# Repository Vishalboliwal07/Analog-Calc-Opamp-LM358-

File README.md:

# Analog Calculator

## Summary
In a world dominated by digital microprocessors, this project explores the principles of analog computing by designing and constructing a functional, purely analog calculator. The core of the system is built around LM358 operational amplifiers configured with specific feedback networks of resistors, capacitors, and diodes. The calculator operates as a parallel processing system where all calculations happen simultaneously based on variable DC voltage or AC signal inputs. The system operates on a dual-rail +/-15V or 30V power supply, establishing a true 0V ground reference to simplify the circuit designs and eliminate the need for a virtual ground.

*Note regarding the power supply: While some project documentation may refer to a +/-30V power rail, the system actually operates on a +/-15V dual-rail supply (which provides a total 30V potential difference). This establishes a true 0V ground reference to simplify the circuit designs and eliminate the need for a virtual ground.*

## Mathematical Functions Supported
The calculator accepts numerical inputs (from 0.01V to 14V) and implements dedicated modular circuits to perform the following operations:
* **Addition:** Utilizes an inverting summing amplifier.
* **Subtraction:** Utilizes a difference amplifier to find the difference between two signals.
* **Multiplication:** Achieved using logarithmic principles (In(A * B) = In(A) + In(B)) via log, summing, and anti-log stages.
* **Division:** Similar to multiplication, but uses a subtraction (difference) stage for the log values.
* **Logarithm:** Uses the exponential current-voltage relationship of a semiconductor diode in the op-amp's feedback path.
* **Anti-Logarithm (Exponential):** Performs the inverse operation of the log amplifier to output an exponential function of the input.
* **Modulus (Absolute Value):** Implements a precision full-wave rectifier using op-amps and diodes.
* **Square Root & Any Root:** Uses an NMOS MOSFET in the feedback loop of the op-amp.
* **Integration:** Converts inputs like a square wave into a triangle wave using a capacitor in the feedback loop.
* **Differentiation:** Converts inputs like a triangle wave into a square wave using a capacitor at the input.

## Key Contributions
* **Parallel Computation Architecture:** Designed a system where buffered input signals are routed to all computational blocks simultaneously, ensuring no source-loading measurement errors.
* **Operation Selection:** Implemented a multi-position switch and an analog multiplexer (MUX) to allow users to select and view a single, clean result without circuit outputs conflicting.
* **Circuit Simulation:** Verified DC operating points, AC frequency responses, and transient behaviors of all individual blocks using LTspice prior to physical builds.
* **PCB Design:** Designed a comprehensive 2-layer PCB layout (11.5cm x 12.5cm) integrating all functional blocks and a dual-rail power supply.

## Results
* **Simulation Success:** LTspice simulations confirmed mathematical accuracy. For example, the adder successfully simulated 4 + 2 = 5.99V, the subtractor simulated 4 - 2 = 1.99V, and the differentiator successfully converted sine waves to cosine waves.
* **Hardware Preparation:** Successfully generated and verified the final Gerber files and Drill files for the PCB layout. 
* **Manufacturing Readiness:** Prepped the board for fabrication, estimating a cost of INR 2432 for standard manufacturing of 5 PCBs.

## Future Scope & Improvements
* **I/O Optimization via Multiplexing:** Integrate analog multiplexers (MUX) and demultiplexers (DEMUX) at the input and output stages to streamline user interaction and make the calculator more intuitive to use. To maintain signal integrity, appropriate compensating resistors will be added to counteract the tradeoff of lower voltages and inherent voltage drops across the MUX/DEMUX components.
* **Architectural Compaction & Resource Sharing:** Optimize the PCB layout and reduce the overall component count by reusing functional blocks. For example, instead of building separate adders for every module, the standalone adder circuit can be shared and routed to serve the internal summing stage of the multiplier and divider. This minimizes redundancy, reduces the footprint, and creates a highly compact design.

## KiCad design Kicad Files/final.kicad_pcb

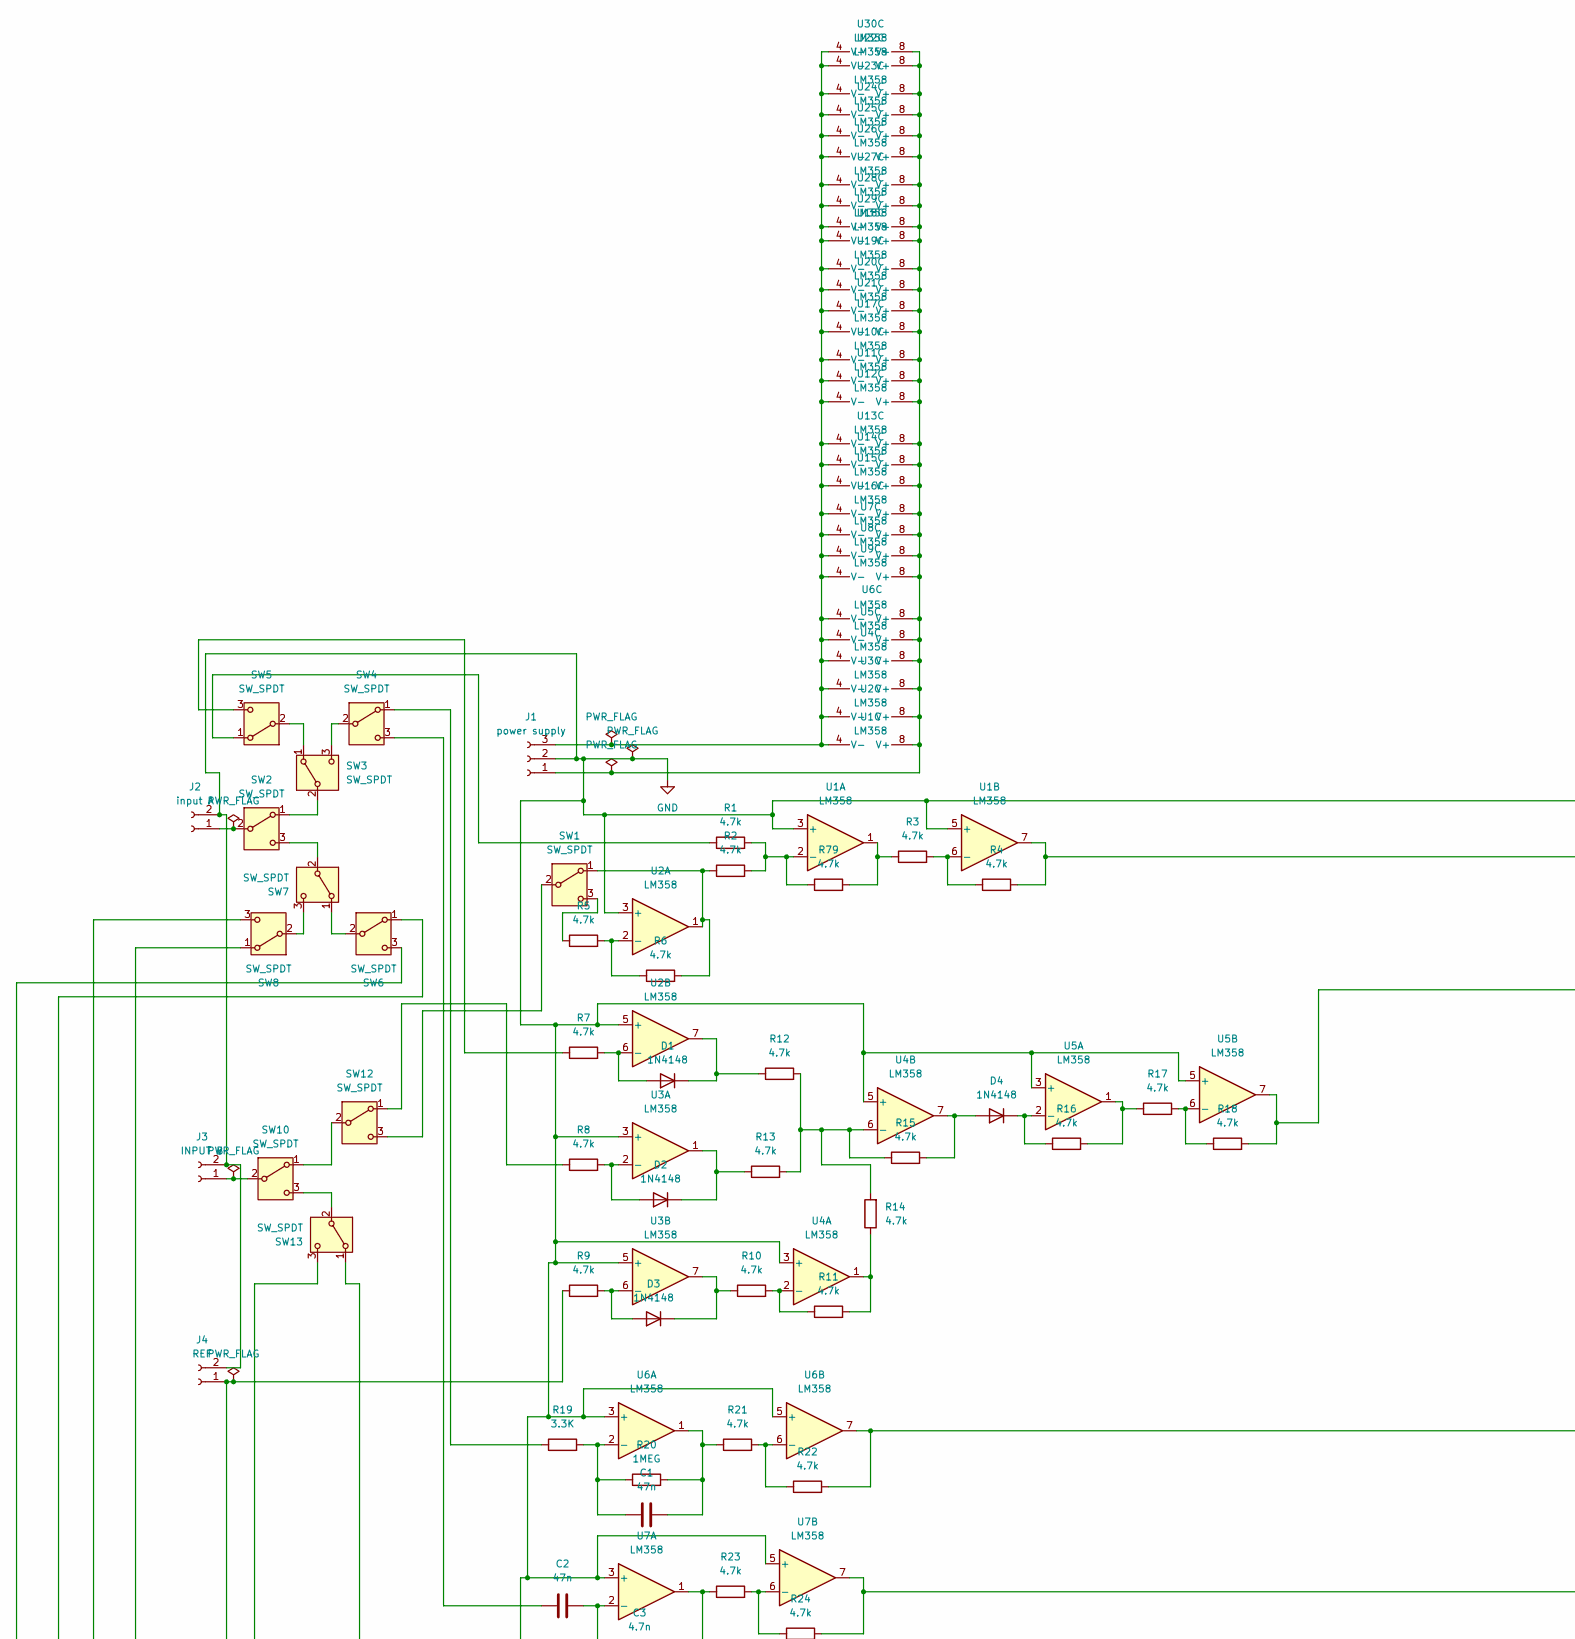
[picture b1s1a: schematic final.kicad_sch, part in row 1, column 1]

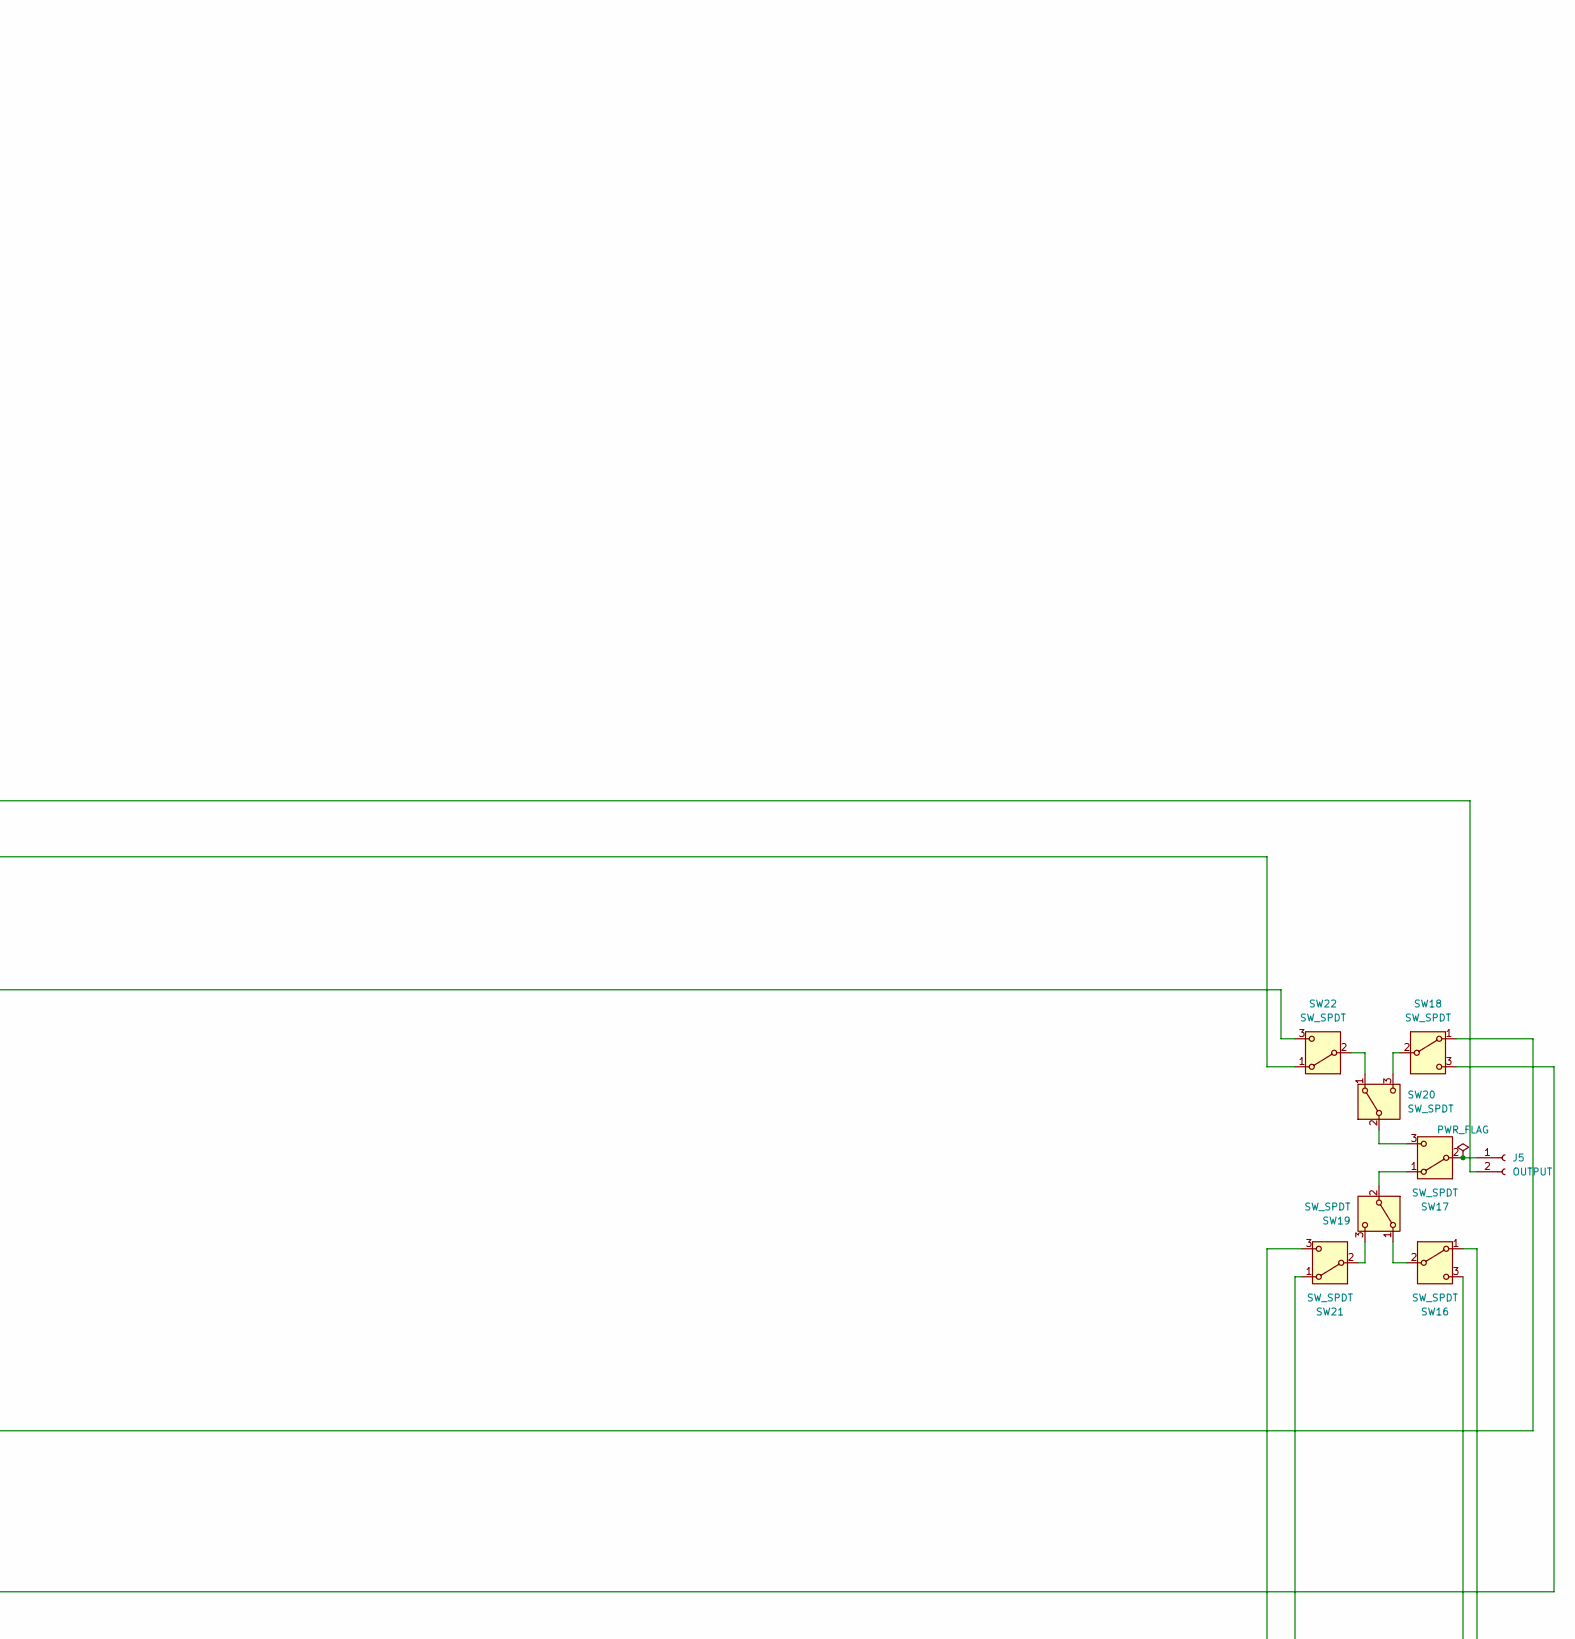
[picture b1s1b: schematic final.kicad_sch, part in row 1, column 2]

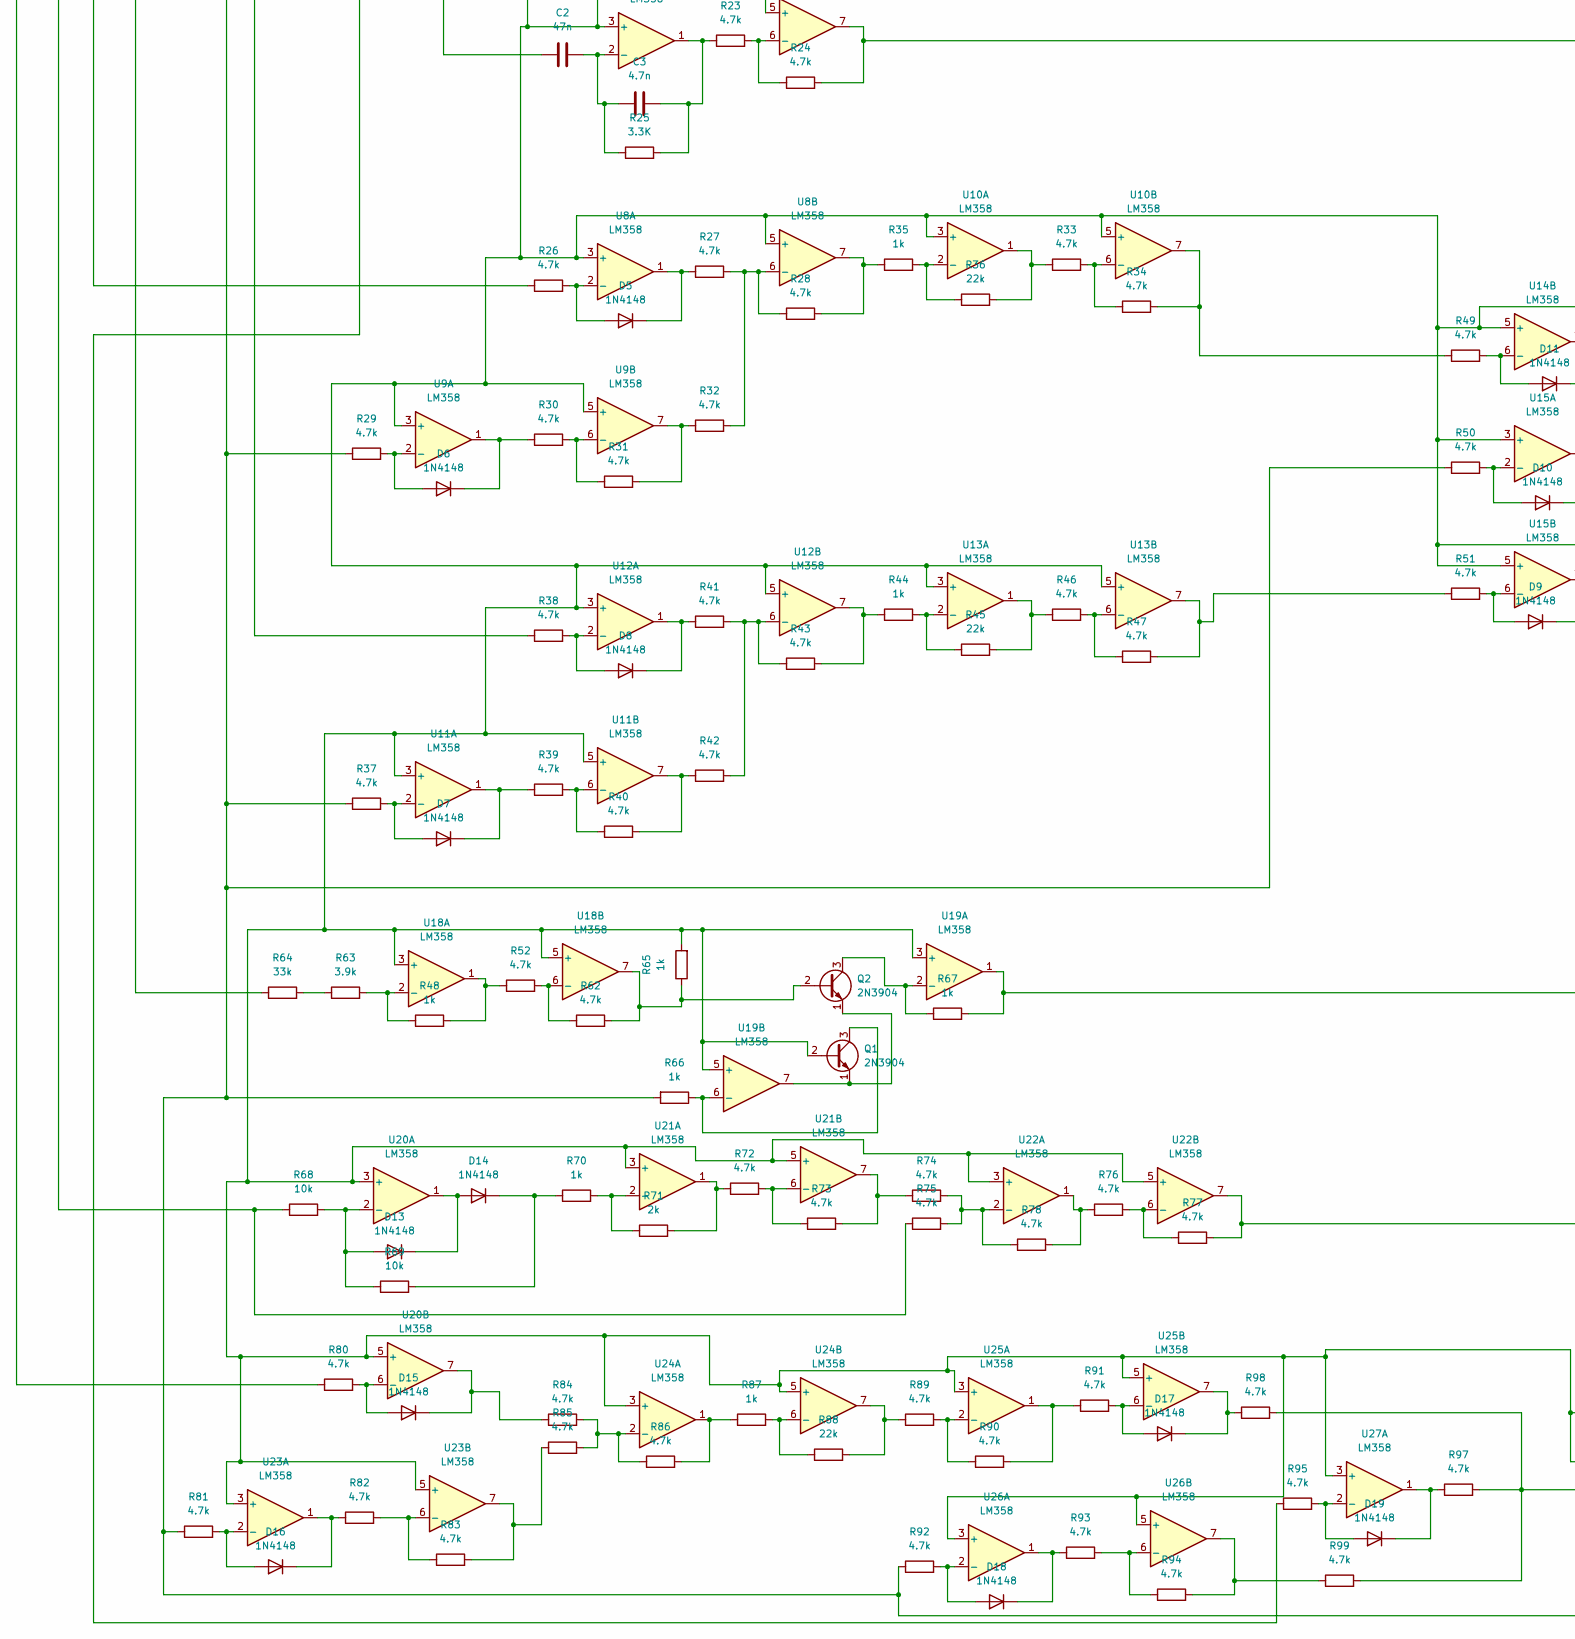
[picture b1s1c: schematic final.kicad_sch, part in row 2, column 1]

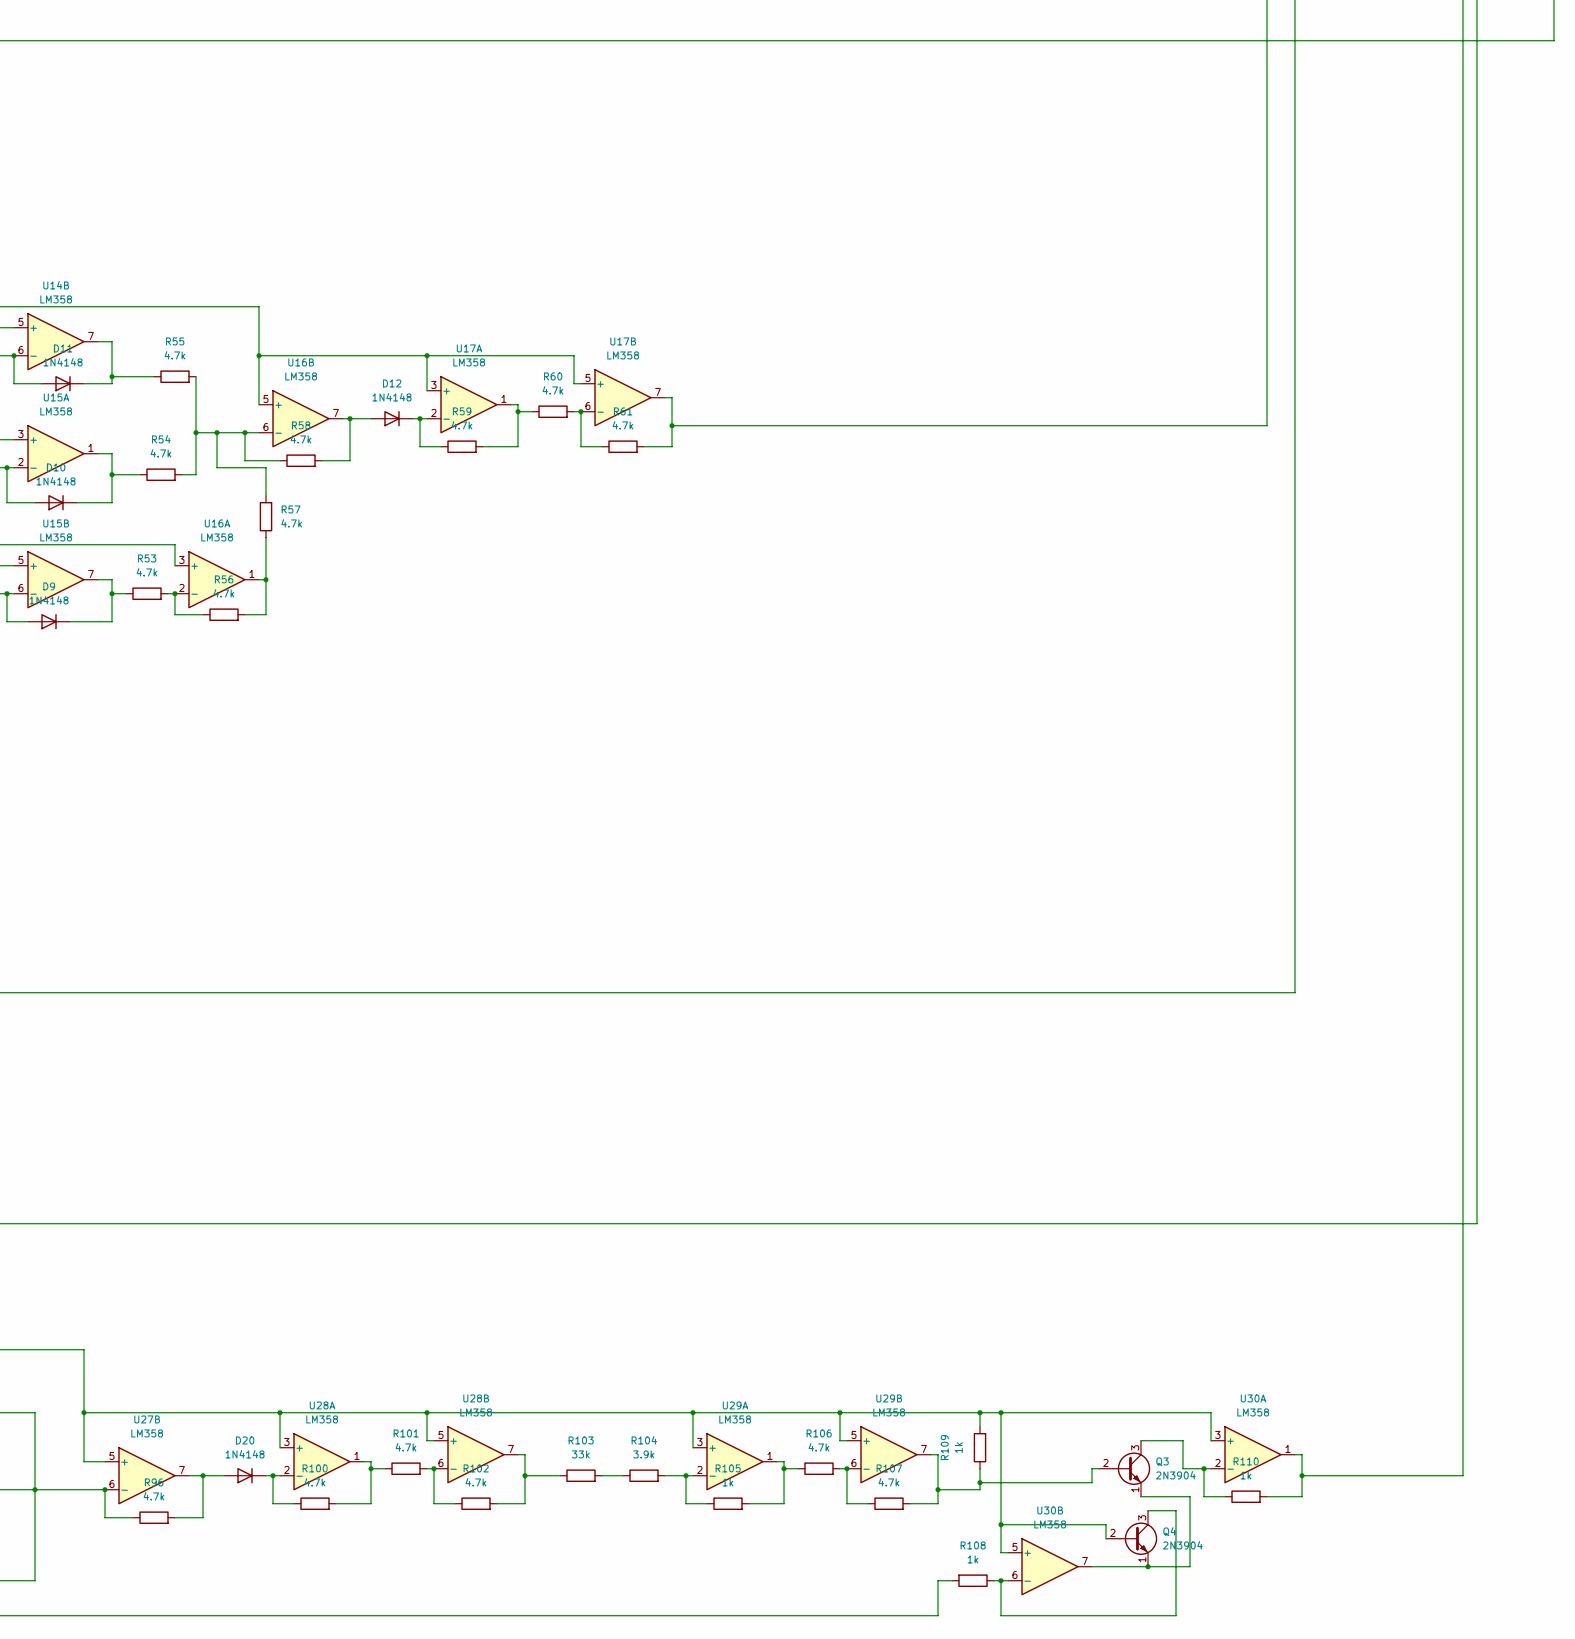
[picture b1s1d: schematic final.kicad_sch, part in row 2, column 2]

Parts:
C1, C2: 47n; C_Disc_D7.5mm_W5.0mm_P7.50mm
C3: 4.7n; C_Disc_D7.5mm_W5.0mm_P7.50mm
D1, D2, D3, D4, D5, D6, D7, D8, D9, D10, D11, D12, D13, D14, D15, D16, D17, D18, D19, D20: 1N4148; D_DO-35_SOD27_P7.62mm_Horizontal
J1: power supply; PinSocket_1x03_P2.54mm_Vertical
J2: input A; PinSocket_1x02_P2.54mm_Vertical
J3: INPUT B; PinSocket_1x02_P2.54mm_Vertical
J4: REF; PinSocket_1x02_P2.54mm_Vertical
J5: OUTPUT; PinSocket_1x02_P2.54mm_Vertical
Q1, Q2, Q3, Q4: 2N3904; TO-92_Inline
R1, R2, R3, R4, R5, R6, R7, R8, R9, R10, R11, R12, R13, R14, R15, R16, R17, R18, R21, R22, R23, R24, R26, R27, R28, R29, R30, R31, R32, R33, R34, R37, R38, R39, R40, R41, R42, R43, R46, R47, R49, R50, R51, R52, R53, R54, R55, R56, R57, R58, R59, R60, R61, R62, R72, R73, R74, R75, R76, R77, R78, R79, R80, R81, R82, R83, R84, R85, R86, R89, R90, R91, R92, R93, R94, R95, R96, R97, R98, R99, R100, R101, R102, R106, R107: 4.7k; R_0805_2012Metric_Pad1.20x1.40mm_HandSolder
R19, R25: 3.3K; R_0805_2012Metric_Pad1.20x1.40mm_HandSolder
R20: 1MEG; R_0805_2012Metric_Pad1.20x1.40mm_HandSolder
R35, R44, R48, R65, R66, R67, R70, R87, R105, R108, R109, R110: 1k; R_0805_2012Metric_Pad1.20x1.40mm_HandSolder
R36, R45, R88: 22k; R_0805_2012Metric_Pad1.20x1.40mm_HandSolder
R63, R104: 3.9k; R_0805_2012Metric_Pad1.20x1.40mm_HandSolder
R64, R103: 33k; R_0805_2012Metric_Pad1.20x1.40mm_HandSolder
R68, R69: 10k; R_0805_2012Metric_Pad1.20x1.40mm_HandSolder
R71: 2k; R_0805_2012Metric_Pad1.20x1.40mm_HandSolder
SW1, SW2, SW3, SW4, SW5, SW6, SW7, SW8, SW10, SW12, SW13, SW16, SW17, SW18, SW19, SW20, SW21, SW22: SW_SPDT; spdt final
U1, U2, U3, U4, U5, U6, U7, U8, U9, U10, U11, U12, U13, U14, U15, U16, U17, U18, U19, U20, U21, U22, U23, U24, U25, U26, U27, U28, U29, U30: LM358; DIP-8_W7.62mm

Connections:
GND: J1.2, J2.2, J3.2, J4.2, J5.2, Q1.2 (B), Q4.2 (B), R65.2, R109.2, U1.3 (+), U1.5 (+), U2.3 (+), U2.5 (+), U3.3 (+), U3.5 (+), U4.3 (+), U4.5 (+), U5.3 (+), U5.5 (+), U6.3 (+), U6.5 (+), U7.3 (+), U7.5 (+), U8.3 (+), U8.5 (+), U9.3 (+), U9.5 (+), U10.3 (+), U10.5 (+), U11.3 (+), U11.5 (+), U12.3 (+), U12.5 (+), U13.3 (+), U13.5 (+), U14.5 (+), U15.3 (+), U15.5 (+), U16.3 (+), U16.5 (+), U17.3 (+), U17.5 (+), U18.3 (+), U18.5 (+), U19.3 (+), U19.5 (+), U20.3 (+), U20.5 (+), U21.3 (+), U21.5 (+), U22.3 (+), U22.5 (+), U23.3 (+), U23.5 (+), U24.3 (+), U24.5 (+), U25.3 (+), U25.5 (+), U26.3 (+), U26.5 (+), U27.3 (+), U27.5 (+), U28.3 (+), U28.5 (+), U29.3 (+), U29.5 (+), U30.3 (+), U30.5 (+)
unnamed: C1.2, R20.2, R21.1, U6.1
unnamed: C3.2, R23.1, R25.2, U7.1
unnamed: D1.2 (A), R7.2, U2.6 (-)
unnamed: D1.1 (K), R12.1, U2.7
unnamed: D2.2 (A), R8.2, U3.2 (-)
unnamed: D2.1 (K), R13.1, U3.1
unnamed: D3.2 (A), R9.2, U3.6 (-)
unnamed: D3.1 (K), R10.1, U3.7
unnamed: D4.2 (A), R15.2, U4.7
unnamed: D4.1 (K), R16.1, U5.2 (-)
unnamed: D5.2 (A), R26.2, U8.2 (-)
unnamed: D5.1 (K), R27.1, U8.1
unnamed: D6.2 (A), R29.2, U9.2 (-)
unnamed: D6.1 (K), R30.1, U9.1
unnamed: D7.2 (A), R37.2, U11.2 (-)
unnamed: D7.1 (K), R39.1, U11.1
unnamed: D8.2 (A), R38.2, U12.2 (-)
unnamed: D8.1 (K), R41.1, U12.1
unnamed: D9.2 (A), R51.2, U15.6 (-)
unnamed: D9.1 (K), R53.1, U15.7
unnamed: D10.2 (A), R50.2, U15.2 (-)
unnamed: D10.1 (K), R54.1, U15.1
unnamed: D11.2 (A), R49.2, U14.6 (-)
unnamed: D11.1 (K), R55.1, U14.7
unnamed: D12.2 (A), R58.2, U16.7
unnamed: D12.1 (K), R59.1, U17.2 (-)
unnamed: D13.2 (A), R68.2, R69.1, U20.2 (-)
unnamed: D13.1 (K), D14.2 (A), U20.1
unnamed: D14.1 (K), R69.2, R70.1
unnamed: D15.2 (A), R80.2, U20.6 (-)
unnamed: D15.1 (K), R84.1, U20.7
unnamed: D16.2 (A), R81.2, U23.2 (-)
unnamed: D16.1 (K), R82.1, U23.1
unnamed: D17.2 (A), R91.2, U25.6 (-)
unnamed: D17.1 (K), R98.1, U25.7
unnamed: D18.2 (A), R92.2, U26.2 (-)
unnamed: D18.1 (K), R93.1, U26.1
unnamed: D19.2 (A), R95.2, U27.2 (-)
unnamed: D19.1 (K), R97.1, U27.1
unnamed: D20.2 (A), R96.2, U27.7
unnamed: D20.1 (K), R100.1, U28.2 (-)
unnamed: J1.1, U1.8 (V+), U2.8 (V+), U3.8 (V+), U4.8 (V+), U5.8 (V+), U6.8 (V+), U7.8 (V+), U8.8 (V+), U9.8 (V+), U10.8 (V+), U11.8 (V+), U12.8 (V+), U13.8 (V+), U14.8 (V+), U15.8 (V+), U16.8 (V+), U17.8 (V+), U18.8 (V+), U19.8 (V+), U20.8 (V+), U21.8 (V+), U22.8 (V+), U23.8 (V+), U24.8 (V+), U25.8 (V+), U26.8 (V+), U27.8 (V+), U28.8 (V+), U29.8 (V+), U30.8 (V+)
unnamed: J1.3, U1.4 (V-), U2.4 (V-), U3.4 (V-), U4.4 (V-), U5.4 (V-), U6.4 (V-), U7.4 (V-), U8.4 (V-), U9.4 (V-), U10.4 (V-), U11.4 (V-), U12.4 (V-), U13.4 (V-), U14.4 (V-), U15.4 (V-), U16.4 (V-), U17.4 (V-), U18.4 (V-), U19.4 (V-), U20.4 (V-), U21.4 (V-), U22.4 (V-), U23.4 (V-), U24.4 (V-), U25.4 (V-), U26.4 (V-), U27.4 (V-), U28.4 (V-), U29.4 (V-), U30.4 (V-)
unnamed: J2.1, SW2.2 (B)
unnamed: J3.1, SW10.2 (B)
unnamed: J4.1, R9.1, R29.1, R37.1, R50.1, R66.2, R81.1, R92.1, R108.2
unnamed: J5.1, SW17.2 (B)
unnamed: Q1.3 (C), R66.1, U19.6 (-)
unnamed: Q1.1 (E), Q2.1 (E), U19.7
unnamed: Q2.2 (B), R62.2, R65.1, U18.7
unnamed: Q2.3 (C), R67.1, U19.2 (-)
unnamed: Q3.2 (B), R107.2, R109.1, U29.7
unnamed: Q3.3 (C), R110.1, U30.2 (-)
unnamed: Q3.1 (E), Q4.1 (E), U30.7
unnamed: Q4.3 (C), R108.1, U30.6 (-)
unnamed: R3.1, R79.2, U1.1
unnamed: R11.2, R14.1, U4.1
unnamed: R16.2, R17.1, U5.1
unnamed: R28.2, R35.1, U8.7
unnamed: R31.2, R32.1, U9.7
unnamed: R33.1, R36.2, U10.1
unnamed: R34.2, R49.1, U10.7
unnamed: R40.2, R42.1, U11.7
unnamed: R43.2, R44.1, U12.7
unnamed: R45.2, R46.1, U13.1
unnamed: R47.2, R51.1, U13.7
unnamed: R48.2, R52.1, U18.1
unnamed: R56.2, R57.1, U16.1
unnamed: R59.2, R60.1, U17.1
unnamed: R63.1, R64.2
unnamed: R71.2, R72.1, U21.1
unnamed: R73.2, R74.1, U21.7
unnamed: R76.1, R78.2, U22.1
unnamed: R83.2, R85.1, U23.7
unnamed: R86.2, R87.1, U24.1
unnamed: R88.2, R89.1, U24.7
unnamed: R90.2, R91.1, U25.1
unnamed: R94.2, R99.1, U26.7
unnamed: R100.2, R101.1, U28.1
unnamed: R102.2, R103.1, U28.7
unnamed: R103.2, R104.1
unnamed: R105.2, R106.1, U29.1
unnamed: R2.1, R6.2, SW1.1 (A), U2.1
unnamed: SW1.2 (B), SW12.3 (C)
unnamed: R5.1, SW1.3 (C)
unnamed: SW2.1 (A), SW3.2 (B)
unnamed: SW2.3 (C), SW7.2 (B)
unnamed: SW3.1 (A), SW5.2 (B)
unnamed: SW3.3 (C), SW4.2 (B)
unnamed: R19.1, SW4.1 (A)
unnamed: C2.1, SW4.3 (C)
unnamed: R1.1, SW5.1 (A)
unnamed: R7.1, SW5.3 (C)
unnamed: R68.1, R75.1, SW6.1 (A)
unnamed: SW6.2 (B), SW7.1 (A)
unnamed: R80.1, SW6.3 (C)
unnamed: SW7.3 (C), SW8.2 (B)
unnamed: R64.1, SW8.1 (A)
unnamed: R26.1, SW8.3 (C)
unnamed: SW10.1 (A), SW12.2 (B)
unnamed: SW10.3 (C), SW13.2 (B)
unnamed: R8.1, SW12.1 (A)
unnamed: R95.1, SW13.1 (A)
unnamed: R38.1, SW13.3 (C)
unnamed: R77.2, SW16.1 (A), U22.7
unnamed: SW16.2 (B), SW19.1 (A)
unnamed: R110.2, SW16.3 (C), U30.1
unnamed: SW17.1 (A), SW19.2 (B)
unnamed: SW17.3 (C), SW20.2 (B)
unnamed: R22.2, SW18.1 (A), U6.7
unnamed: SW18.2 (B), SW20.3 (C)
unnamed: R24.2, SW18.3 (C), U7.7
unnamed: SW19.3 (C), SW21.2 (B)
unnamed: SW20.1 (A), SW22.2 (B)
unnamed: R67.2, SW21.1 (A), U19.1
unnamed: R61.2, SW21.3 (C), U17.7
unnamed: R4.2, SW22.1 (A), U1.7
unnamed: R18.2, SW22.3 (C), U5.7
unnamed: R1.2, R2.2, R79.1, U1.2 (-)
unnamed: R3.2, R4.1, U1.6 (-)
unnamed: R5.2, R6.1, U2.2 (-)
unnamed: R10.2, R11.1, U4.2 (-)
unnamed: R12.2, R13.2, R14.2, R15.1, U4.6 (-)
unnamed: R17.2, R18.1, U5.6 (-)
unnamed: C1.1, R19.2, R20.1, U6.2 (-)
unnamed: R21.2, R22.1, U6.6 (-)
unnamed: C2.2, C3.1, R25.1, U7.2 (-)
unnamed: R23.2, R24.1, U7.6 (-)
unnamed: R27.2, R28.1, R32.2, U8.6 (-)
unnamed: R30.2, R31.1, U9.6 (-)
unnamed: R35.2, R36.1, U10.2 (-)
unnamed: R33.2, R34.1, U10.6 (-)
unnamed: R39.2, R40.1, U11.6 (-)
unnamed: R41.2, R42.2, R43.1, U12.6 (-)
unnamed: R44.2, R45.1, U13.2 (-)
unnamed: R46.2, R47.1, U13.6 (-)
unnamed: R53.2, R56.1, U16.2 (-)
unnamed: R54.2, R55.2, R57.2, R58.1, U16.6 (-)
unnamed: R60.2, R61.1, U17.6 (-)
unnamed: R48.1, R63.2, U18.2 (-)
unnamed: R52.2, R62.1, U18.6 (-)
unnamed: R70.2, R71.1, U21.2 (-)
unnamed: R72.2, R73.1, U21.6 (-)
unnamed: R74.2, R75.2, R78.1, U22.2 (-)
unnamed: R76.2, R77.1, U22.6 (-)
unnamed: R82.2, R83.1, U23.6 (-)
unnamed: R84.2, R85.2, R86.1, U24.2 (-)
unnamed: R87.2, R88.1, U24.6 (-)
unnamed: R89.2, R90.1, U25.2 (-)
unnamed: R93.2, R94.1, U26.6 (-)
unnamed: R96.1, R97.2, R98.2, R99.2, U27.6 (-)
unnamed: R101.2, R102.1, U28.6 (-)
unnamed: R104.2, R105.1, U29.2 (-)
unnamed: R106.2, R107.1, U29.6 (-)

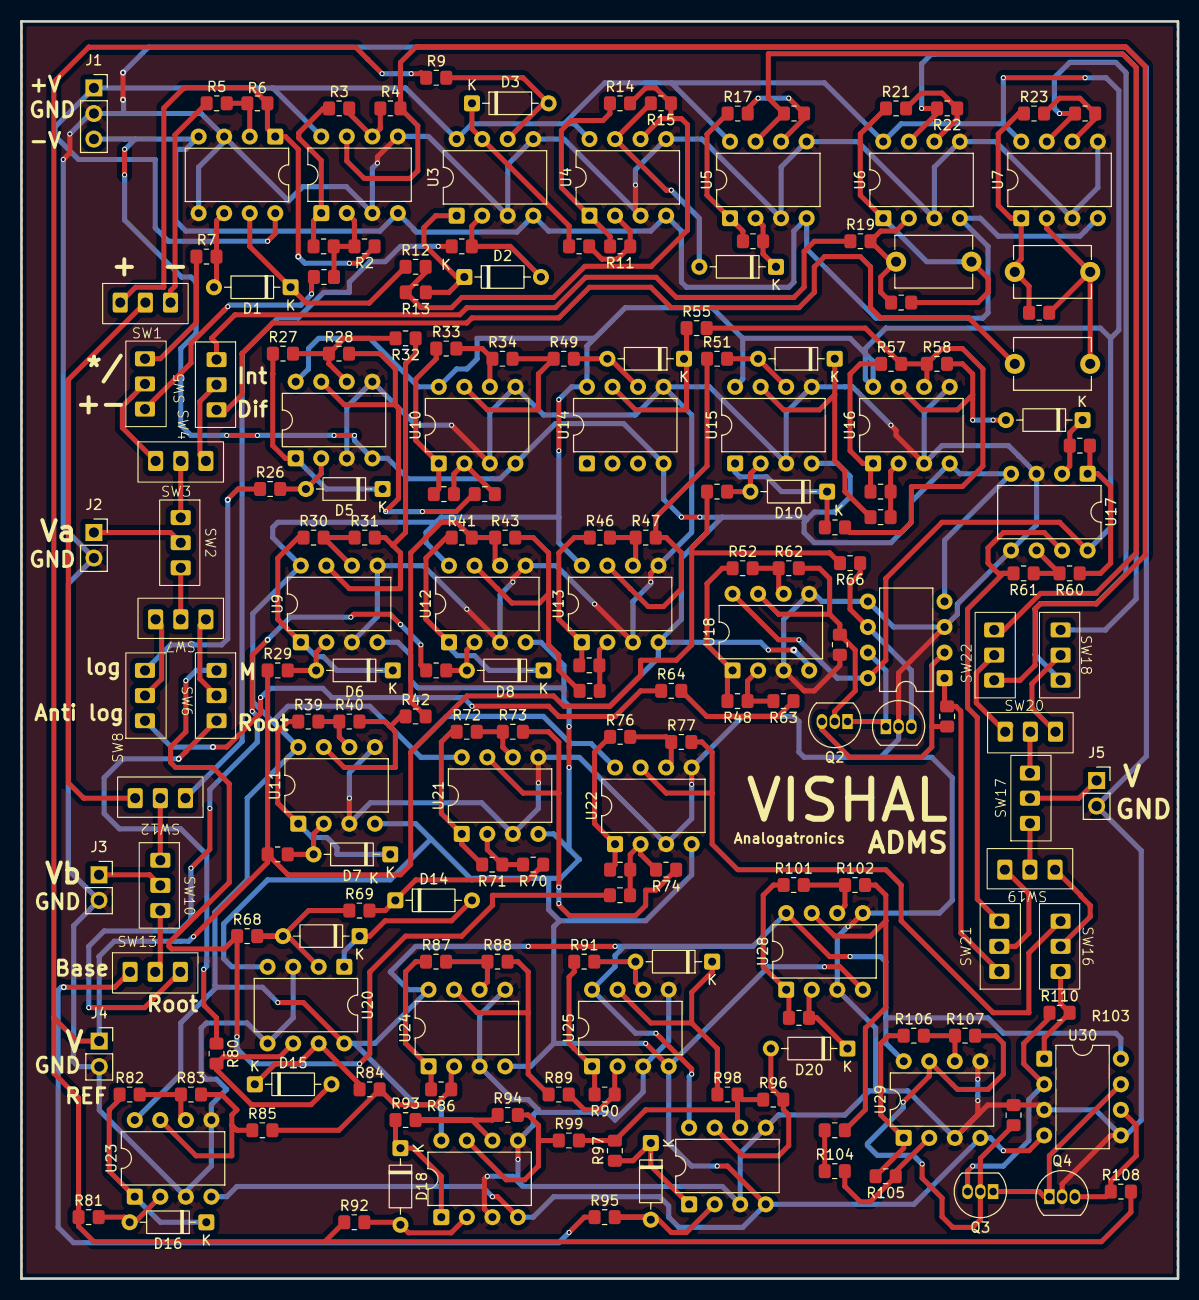
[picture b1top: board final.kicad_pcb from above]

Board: 2 copper layers, 115.0 x 125.0 mm, 190 parts (0 on the bottom side), 155 nets.

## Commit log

2026-02-28 Create Images
2026-03-06 Update README with image and power supply note
    Added image and clarified power supply details in the README.
